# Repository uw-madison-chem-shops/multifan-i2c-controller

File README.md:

# multifan i2c controller

# PCB

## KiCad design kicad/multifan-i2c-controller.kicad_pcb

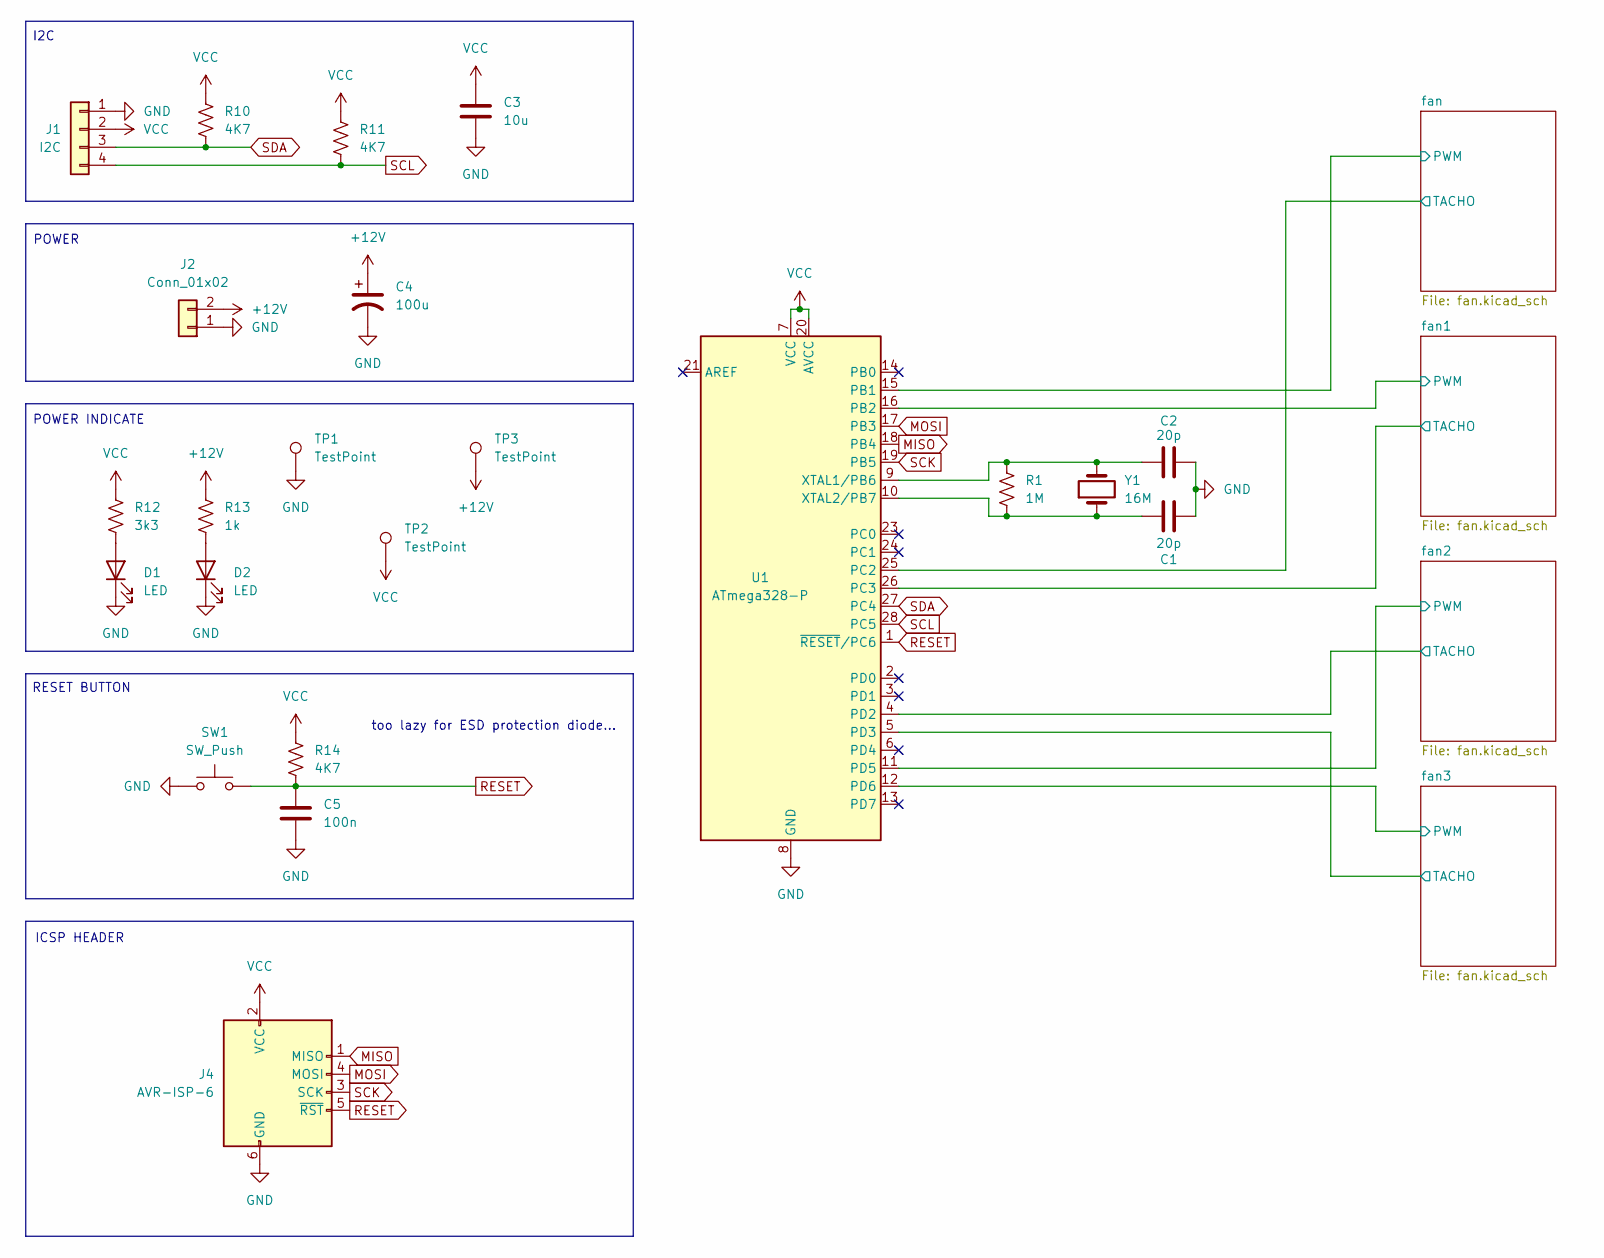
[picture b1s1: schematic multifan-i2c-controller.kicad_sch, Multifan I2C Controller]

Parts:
C1, C2: 20p; C_1206_3216Metric_Pad1.33x1.80mm_HandSolder
C3: 10u; C_1206_3216Metric_Pad1.33x1.80mm_HandSolder
C4: 100u; CP_Radial_D7.5mm_P2.50mm
C5: 100n; C_1206_3216Metric_Pad1.33x1.80mm_HandSolder
D1, D2: LED; LED_1206_3216Metric_Pad1.42x1.75mm_HandSolder
J1: I2C; Molex_KK-254_AE-6410-04A_1x04_P2.54mm_Vertical
J2: Conn_01x02; Molex_KK-254_AE-6410-02A_1x02_P2.54mm_Vertical
J4: AVR-ISP-6; PinHeader_2x03_P2.54mm_Vertical
R1: 1M; R_1206_3216Metric
R10, R11, R14: 4K7; R_1206_3216Metric
R12: 3k3; R_1206_3216Metric
R13: 1k; R_1206_3216Metric
SW1: SW_Push; SW_Push_1P1T_NO_6x6mm_H9.5mm
TP1, TP2, TP3: TestPoint; TestPoint_Loop_D2.60mm_Drill1.6mm_Beaded
U1: ATmega328-P; DIP-28_W7.62mm
Y1: 16M; Crystal_HC49-U_Vertical

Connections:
+12V: C4.1, J2.2, R13.1, TP3.1; also elsewhere on the board
/fan1/PWM: U1.16 (PB2); also elsewhere on the board
/fan1/TACHO: U1.26 (PC3); also elsewhere on the board
/fan2/PWM: U1.11 (PD5); also elsewhere on the board
/fan2/TACHO: U1.4 (PD2); also elsewhere on the board
/fan3/PWM: U1.12 (PD6); also elsewhere on the board
/fan3/TACHO: U1.5 (PD3); also elsewhere on the board
/fan/PWM: U1.15 (PB1); also elsewhere on the board
/fan/TACHO: U1.25 (PC2); also elsewhere on the board
GND: C1.1, C2.2, C3.2, C4.2, C5.2, D1.1 (K), D2.1 (K), J1.1, J2.1, J4.6 (GND), SW1.1, TP1.1, U1.8 (GND), U1.22 (GND); also elsewhere on the board
MISO: J4.1 (MISO), U1.18 (PB4)
MOSI: J4.4 (MOSI), U1.17 (PB3)
unnamed: D1.2 (A), R12.2
unnamed: D2.2 (A), R13.2
unnamed: C2.1, R1.1, U1.9 (XTAL1/PB6), Y1.2
unnamed: C1.2, R1.2, U1.10 (XTAL2/PB7), Y1.1
RESET: C5.1, J4.5 (~RST), R14.2, SW1.2, U1.1 (~RESET/PC6)
SCK: J4.3 (SCK), U1.19 (PB5)
SCL: J1.4, R11.2, U1.28 (PC5)
SDA: J1.3, R10.2, U1.27 (PC4)
VCC: C3.1, J1.2, J4.2 (VCC), R10.1, R11.1, R12.1, R14.1, TP2.1, U1.7 (VCC), U1.20 (AVCC); also elsewhere on the board

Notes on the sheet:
POWER INDICATE
RESET BUTTON
POWER
I2C
too lazy for ESD protection diode...
ICSP HEADER

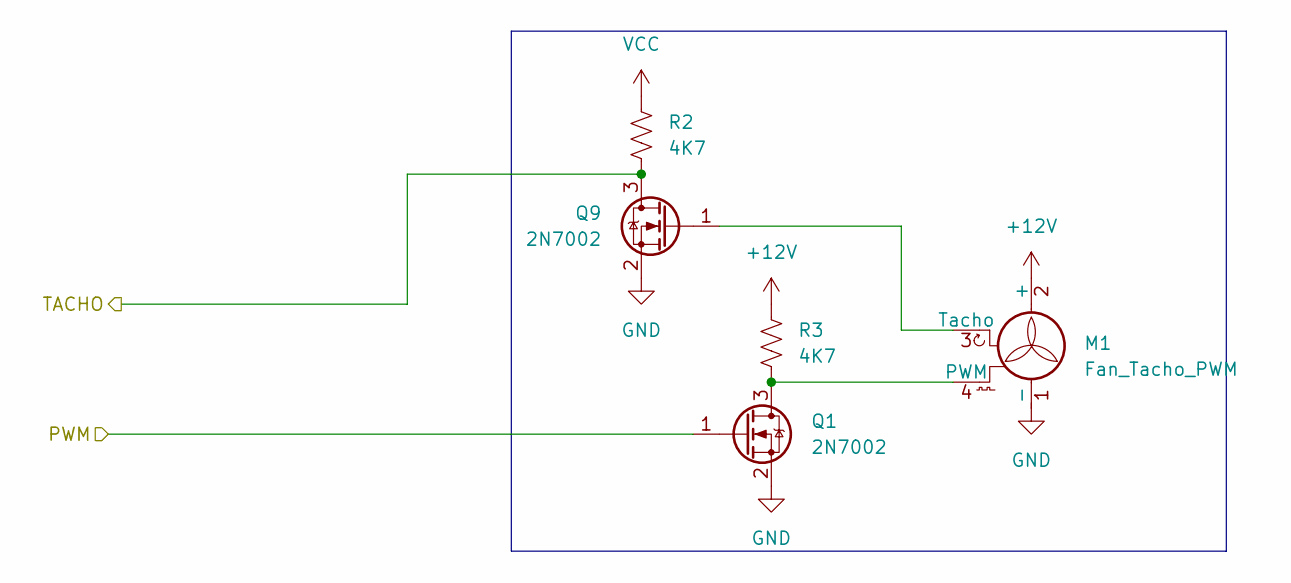
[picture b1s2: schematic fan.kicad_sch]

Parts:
M1: Fan_Tacho_PWM; PinHeader_1x04_P2.54mm_Vertical
Q1, Q9: 2N7002; SOT-23
R2, R3: 4K7; R_1206_3216Metric

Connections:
+12V: M1.2 (+), R3.1; also elsewhere on the board
/fan/PWM: Q1.1 (G); also elsewhere on the board
/fan/TACHO: Q9.3 (D), R2.2; also elsewhere on the board
GND: M1.1 (-), Q1.2 (S), Q9.2 (S); also elsewhere on the board
unnamed: M1.4 (PWM), Q1.3 (D), R3.2
unnamed: M1.3 (Tacho), Q9.1 (G)
VCC: R2.1; also elsewhere on the board

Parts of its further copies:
M2, M3, M4: Fan_Tacho_PWM; PinHeader_1x04_P2.54mm_Vertical
Q2, Q3, Q4, Q10, Q11, Q12: 2N7002; SOT-23
R4, R5, R6, R7, R8, R9: 4K7; R_1206_3216Metric

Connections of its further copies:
+12V: M2.2 (+), M3.2 (+), M4.2 (+), R5.1, R7.1, R9.1; also elsewhere on the board
/fan1/PWM: Q2.1 (G); also elsewhere on the board
/fan1/TACHO: Q10.3 (D), R4.2; also elsewhere on the board
/fan2/PWM: Q3.1 (G); also elsewhere on the board
/fan2/TACHO: Q11.3 (D), R6.2; also elsewhere on the board
/fan3/PWM: Q4.1 (G); also elsewhere on the board
/fan3/TACHO: Q12.3 (D), R8.2; also elsewhere on the board
GND: M2.1 (-), M3.1 (-), M4.1 (-), Q2.2 (S), Q3.2 (S), Q4.2 (S), Q10.2 (S), Q11.2 (S), Q12.2 (S); also elsewhere on the board
unnamed: M2.4 (PWM), Q2.3 (D), R5.2
unnamed: M2.3 (Tacho), Q10.1 (G)
unnamed: M3.4 (PWM), Q3.3 (D), R7.2
unnamed: M3.3 (Tacho), Q11.1 (G)
unnamed: M4.4 (PWM), Q4.3 (D), R9.2
unnamed: M4.3 (Tacho), Q12.1 (G)
VCC: R4.1, R6.1, R8.1; also elsewhere on the board

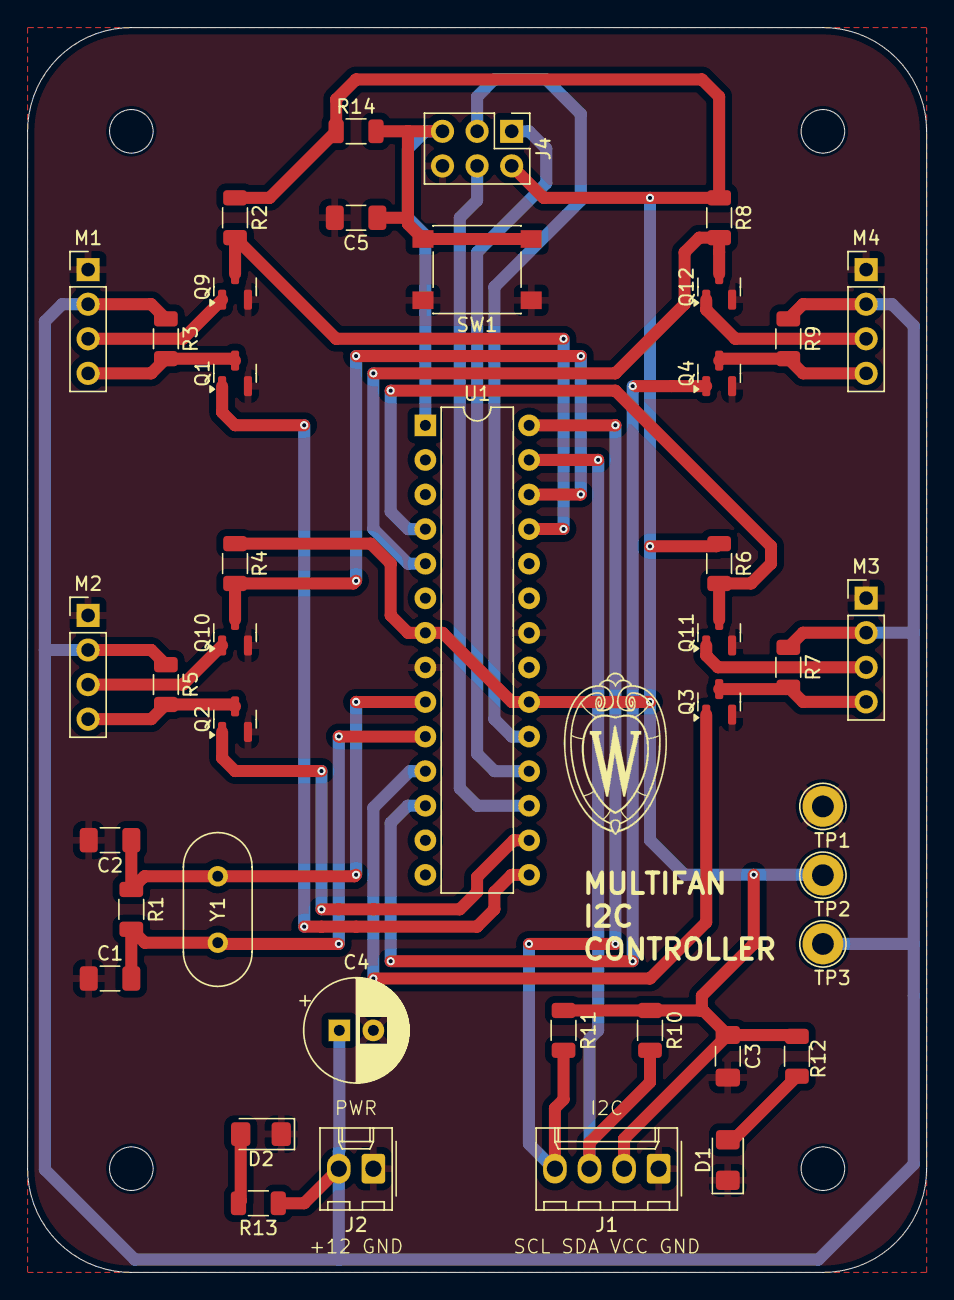
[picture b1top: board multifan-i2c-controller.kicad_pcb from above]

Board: 2 copper layers, 66.0 x 91.4 mm, 42 parts (0 on the bottom side), 29 nets.

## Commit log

2024-03-27 readme
2024-03-27 first kicad checkpoint
2024-04-01 basic layout
2024-04-09 Finished PCB
2024-04-09 Finished PCB (#1)
2024-05-09 revA
2024-06-10 firmware
